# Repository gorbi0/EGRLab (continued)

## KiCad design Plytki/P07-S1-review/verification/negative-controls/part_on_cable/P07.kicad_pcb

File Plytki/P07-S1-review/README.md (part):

# P07 DRIVE — S1, schemat pod moduł IBT-2 (2 × BTS7960B)

*5.10.2026, sesja w chmurze według `Plytki/Format-S1/zadania/ZADANIE-P07-S1.md`. Baza: `origin/pelny-s1`. Pinout P04 R3 z `origin/p04-r3-pcb` (702732a7, `reference/P04-R3-J_BP.csv`).*

**Status (6.10): schemat z decyzjami użytkownika 5.10 i uproszczeniami 6.10 gotowy (ERC 0, kontrole 16/16 i 27/27). PCB NIEDOMKNIĘTE — po uproszczeniach 1–4 zostało 13 przerw sygnałowych (sekcja „PCB — stan”); paczki produkcyjnej nie ma.** Sprzętu nie zmontowano ani nie zmierzono. Moduł IBT-2 zmierzono tylko bez zasilania (POMIARY A–C); kroki D i E nie są zrobione.

## Co to jest

Płytka nośna testera w stosie S1: **poziom 5, sloty S2–S3, klasa 2/3 (106,5 × 100 mm)**. Moduł IBT-2 stoi poza stosem, na ściance obudowy, i łączy się z P07 taśmą 8 żył (J5) oraz czterema parami przewodów 2,0 mm² (J1–J4). Z v6.1 (Pololu 1451 / VNH5019) zostają: własny bocznik Kelvin 5 mΩ + INA240A2 + MCP3201 (ITEST), okno OC z zatrzaskiem, KPWR i otwarty kolektor na SAFE_N. To nie jest zamiana pin w pin. W trybie LOGGER mostek nie jest połączony z ECU — robi to dopiero port TEST na panelu (P11).

| Arkusz | Zawartość |
|---|---|
| P07 | 5VA_P07 (R50 10 Ω), 3V3A_P07 (MCP1702), odsprzęganie, arkusze |
| MOC | J1 VMOTOR, TVS SMCJ18A, C1 220 µF, KPWR K1 (G2RL-1-E **DC5, cewka z 5V_SYS**) z Q1 AO3400A, C9 10 µF i clampem 15 V do 5V_SYS, R4 1 k (wstępne ładowanie), J2 B+/B−, J3 M+/M−, RSH1, J4 TEST |
| ANA | R6/R7 Kelvin, INA240A2, MCP1525, U3 (bufor ADC + REF_BUF), dzielnik ITEST, U4 (OC_HIGH), TLV1702 |
| DIG | MCP3201 (posiadany DIP8), 74LVC125 SPI (DOUT trójstanowy), przejście SUP5 5 V → 3,3 V |
| LOGIKA | MCP120 ×2, odbiorniki Ioff 74LVC125 (od 6.10 tylko MOTOR_INA / INB), 74LVC14 (Schmitt), 3 × 74HC08, 74HC74 (OC_GOOD, NO_TRIP), Q2 na SAFE_N |
| MODUL | PTC → 5V_MOD, 74AHCT125 (3,3 → 5 V z OE), J5, R43 10 Ω w masie modułu, diagnostyka IS (dzielnik + clamp, próg na P03) |
| ZLACZA | J_BP1, J_BP2 |
| SERWIS | J_SV2 z 9 rezystorami przy węzłach (od 6.10; było J_SV1 + J_SV2, 20 kołków) |

Obliczenia: `docs/PROJEKT.md`. Wiązki: `docs/WIAZKA-MODUL.md`. BOM S1: `docs/BOM.csv`, `docs/zakupy.csv` (132 części + wiązka W5; z rejestru INA240A2, MCP3201-BI/P i 2 × 74LVC125AD, reszta nowa).

## Krawędź A (kontrakt dla P12)

| Pin | J_BP1 (S2, x płytki 26,5 / stosu 80,0) | J_BP2 (S3, x płytki 80,0 / stosu 133,5) |
|---|---|---|
| 2 | ADC_SCLK ← P03 | MOTOR_PERMIT ← P04 |
| 4 | ADC_DOUTA → P03 (wspólna, CS) | PWM_OUT ← P04 |
| 6 | CS_ITEST_N ← P03 | ARM_CLK ← P04 |
| 8 | MOTOR_INA ← P03 | DRIVE_OK → P04 |
| 10 | MOTOR_INB ← P03 | 5V_SYS |
| 12 | ENA_DIAG → P03 | 5V_SYS |
| 14 | ENB_DIAG → P03 | 3V3_IO |
| 16 | GND (rezerwa) | SAFE_N (węzeł OC) |

Nieparzyste piny to GND; złącza IDC 2 × 8 kątowe obudowane, pin 1 od mniejszego x. ADC_SCLK / ADC_DOUTA są na pinach 2/4 jak J_BP2 P03 R6, P05 R3 i J_BP P06 R2. Sieci P04 mają te same numery pinów co J_BP2 P04 R3 (2/4/6/8/16). **Dwa złącza zamiast jednego 2 × 10 z budżetu S1 §8:** 12 sygnałów i 3 piny zasilania nie mieszczą się w 10 parzystych pinach. Kierunki i drugi koniec: `docs/J_BP.csv`.

## Krawędź B (serwis)

Od 6.10 (uproszczenie 1) **jedna listwa J_SV2** (S3, x 63,5–96,5, 12 kołków): GND, 5V_SYS, 5VA_P07, 3V3A_P07, KPWR_COIL_LOW, SAFE_OK, OC_LOCAL_N, OC_GOOD, DRIVE_OK (1 k), GND, I_T_OUT (10 k), GND. Zwarcie kołka OC_LOCAL_N do GND (przez 1 k) wymusza OC — próba odbiorcza zatrzasku. RPWM / LPWM / EN / IS mierzy się na listwie modułu, która jest poza stosem. `docs/SERWIS.csv`.

## Kontrole (`src/run_schematic.py`; w chmurze `scripts/egrlab-docker python3 src/run_schematic.py`, ok. 1 min)

| Kontrola | Wynik |
|---|---|
| ERC | **0** na 8 arkuszach |
| Netlista pin po pinie względem `parts.py` | **448/448**, 132 części, 101 sieci (po uproszczeniach 6.10) |
| `verify_electrical.py` | **16/16**, mutacje **23/23**, próba zerowa czysta |
| `verify_s1.py` (S1 i kontrakty P12 / P03 R6 / P04 R3) | **27/27**, mutacje **26/26**, próba zerowa czysta (od 6.10 jedna listwa: 5 kontroli J_SV1 odpada, dochodzą `SV-ONLY-J_SV2` i `SRV-REQUIRED-NODES`) |
| Powierzchnia (`powierzchnia.py`) | 69 % metodą P06 R2 (tam 41 %); wnętrze bez złączy krawędzi 50 %, z 1206 od spodu 37 % |

`verify_electrical.py` symuluje logikę na wyeksportowanej netliście: modele bramek według wartości części, podciąganie przez najmniejszą rezystancję, komparator i nadzorcy jako otwarte kolektory, 74HC74 z PRE/CLR i zboczem. Tabela 2304 wierszy pokazuje, że **bez MOTOR_PERMIT, bez SAFE_N, przy OC albo złych szynach wszystkie wejścia modułu (RPWM, LPWM, R_EN, L_EN) są L**, a KPWR wyłączony. Do tego martwe szyny, otwarte taśmy, zawieszona bramka AND (blokuje ją OE bufora), 11 kroków sekwencji zatrzasku (brak samoczynnego uzbrojenia, ARM przy PERMIT = H nie uzbraja, ARM w trakcie OC nie kasuje), progi OC w narożnikach (+8,01…+8,11 A / −7,99…−8,03 A), skala ITEST, moce bocznika i R4, cewka 5 V z 5V_SYS, bramka Q1 i clamp KPWR, TVS, próg IS i rozdział mas. Raporty: `verification/QA.md`, `electrical-checks.json`, `s1-checks.json`, `powierzchnia.json`; PDF `output/pdf/P07-S1-schemat.pdf`.

## Decyzje (sporne oznaczone)

1. **Mapowanie VNH5019 → BTS7960:** RPWM = PWM & MOTOR_INA, LPWM = PWM & MOTOR_INB, R_EN = L_EN = DRIVE_EN. Hamowanie i stany INA = INB jak w VNH5019. Firmware bez zmian w sterowaniu.
2. **Blokada w trzech warstwach:** bramki AND (MOTOR_PERMIT · SAFE_N · OC_GOOD · RAILS_OK), OE bufora 74AHCT125 i KPWR. 74HC244 modułu jest stale aktywny (OE na GND), więc moduł sam niczego nie blokuje.
3. **DRIVE_OK = RAILS_OK & NO_TRIP** (nowy drugi przerzutnik). Przy starcie bez ARM DRIVE_OK = 1, więc INTERLOCK na P04 nie blokuje LOGGERA ani SENSOR. Po OC DRIVE_OK = 0 aż do ARM. v6.1 miało DRIVE_OK = RAILS_OK.
4. **Logika na 3V3_IO** (jak P04), analog na lokalnych 5VA / 3V3A (jak P06 R2). Odbiorniki z Ioff tylko tam, gdzie drugi koniec może mieć inne zasilanie (P03: MOTOR_INA/INB, CS, SCLK) oraz dla MOTOR_PERMIT / PWM_OUT. SAFE_N wchodzi przez 1 k na Schmitt 74LVC14 (zbocze RC ok. 10 µs na P04), bez podciągania na P07, z 1 M do GND (otwarta taśma = SAFE_OK L).
5. **R4 1 kΩ równolegle do styków KPWR (zostaje — decyzja użytkownika 5.10):** ładuje 330 µF modułu, żeby styk nie zamykał się na pusty kondensator (spawanie). Cena: przy otwartym KPWR B+ modułu jest na 91 % VMOTOR przez 1 k; prąd silnika ≤ 17 mA, przy zwarciu 0,28 W.
6. **KPWR to przekaźnik G2RL-1-E DC5 z cewką na 5V_SYS** (decyzja użytkownika 5.10; było DC12 z VMOTOR), nie tranzystor: galwaniczne odłączenie i brak strat przy 10 A (MOSFET z P02 dałby ok. 2 W bez radiatora). Cewka 80 mA przy 98–102 % napięcia znamionowego, Q1 AO3400A (źródło na GND, bramka wprost z 74HC08 przez 100 Ω — NPN potrzebowałby ok. 6 mA bazy z HC przy 3,3 V), clamp 1N4148W + 15 V do 5V_SYS (VDS ≤ 20,8 V), C9 10 µF przy cewce. Obwód cewki w domenie GND, styki w domenie PGND. Footprint bez zmian.
7. **Masy:** GND i PGND rozdzielone na P07, wspólny punkt na P02 R4. MOD_GND przez 10 Ω. Działa przy masie modułu połączonej z B− i przy rozdzielonej (`docs/PROJEKT.md`).
8. **Sporne — filtr ITEST τ 0,26 ms** (C7 100 nF C0G): antyaliasing przy 2 kS/s.
9. **OC ±8 A:** ≥ 115 % prądu pracy 6 A, poniżej nasycenia INA240A2 przy najniższym 5VA. „10 A w próbie” = bierna kwalifikacja toru jak w P06 (E15) — decyzja użytkownika 5.10; aktywny mostek nie podaje 10 A.
10. **ENA_DIAG / ENB_DIAG:** H = prąd gałęzi powyżej ok. 1,3–5,8 A (od 6.10: próg na wejściu P03, bez Schmitta) albo poziom błędu IS (przyjęte 5.10; firmware dostosuje się później). Znaczenie inne niż w VNH5019 (tam L = błąd).
11. Wyjątki od „nowe = SMD 1206”: R4 2512 (moc), C1 elektrolit, RSH1 2512 Kelvin (jak P06 R2), K1, MCP3201 w posiadanym DIP8, TO-92 jak w P06 R2.

## Wymagania dla layoutu (sesja lokalna)

- J4 (TEST) przy krawędzi x = 0; J1–J3 najlepiej tam samo, żeby pętla 10 A była krótka. Tor 10 A ≥ 4 mm na obu warstwach, zszyty przelotkami; bez przelotek w polach RSH1; para Kelvina jak w P06 R2.
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
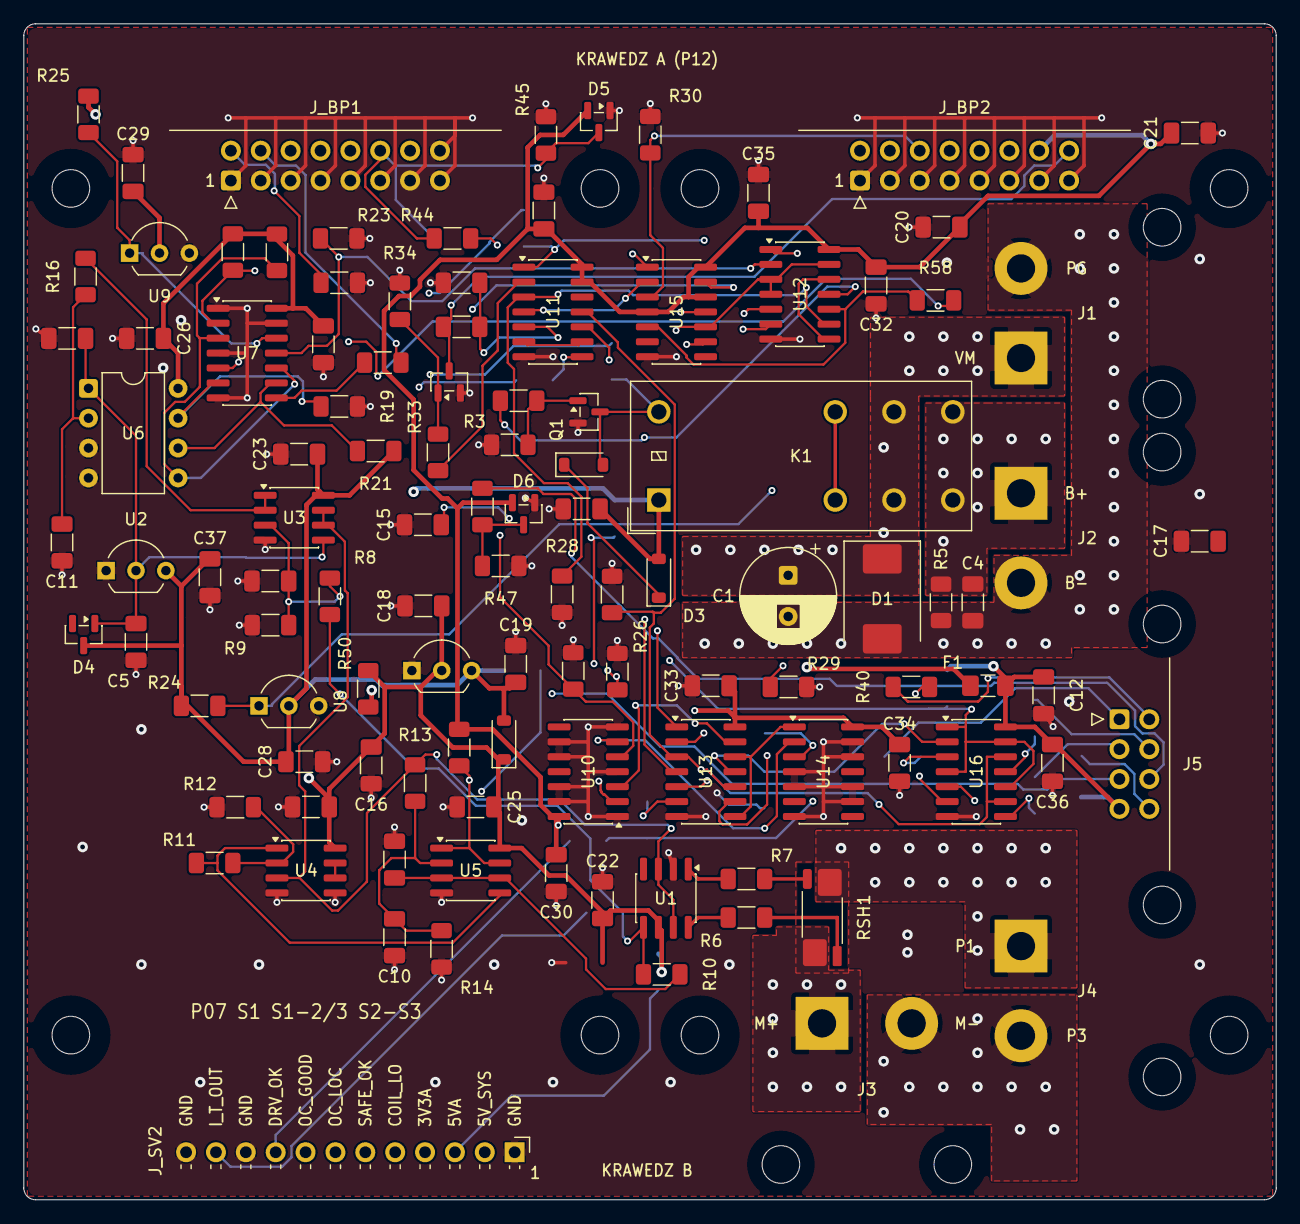
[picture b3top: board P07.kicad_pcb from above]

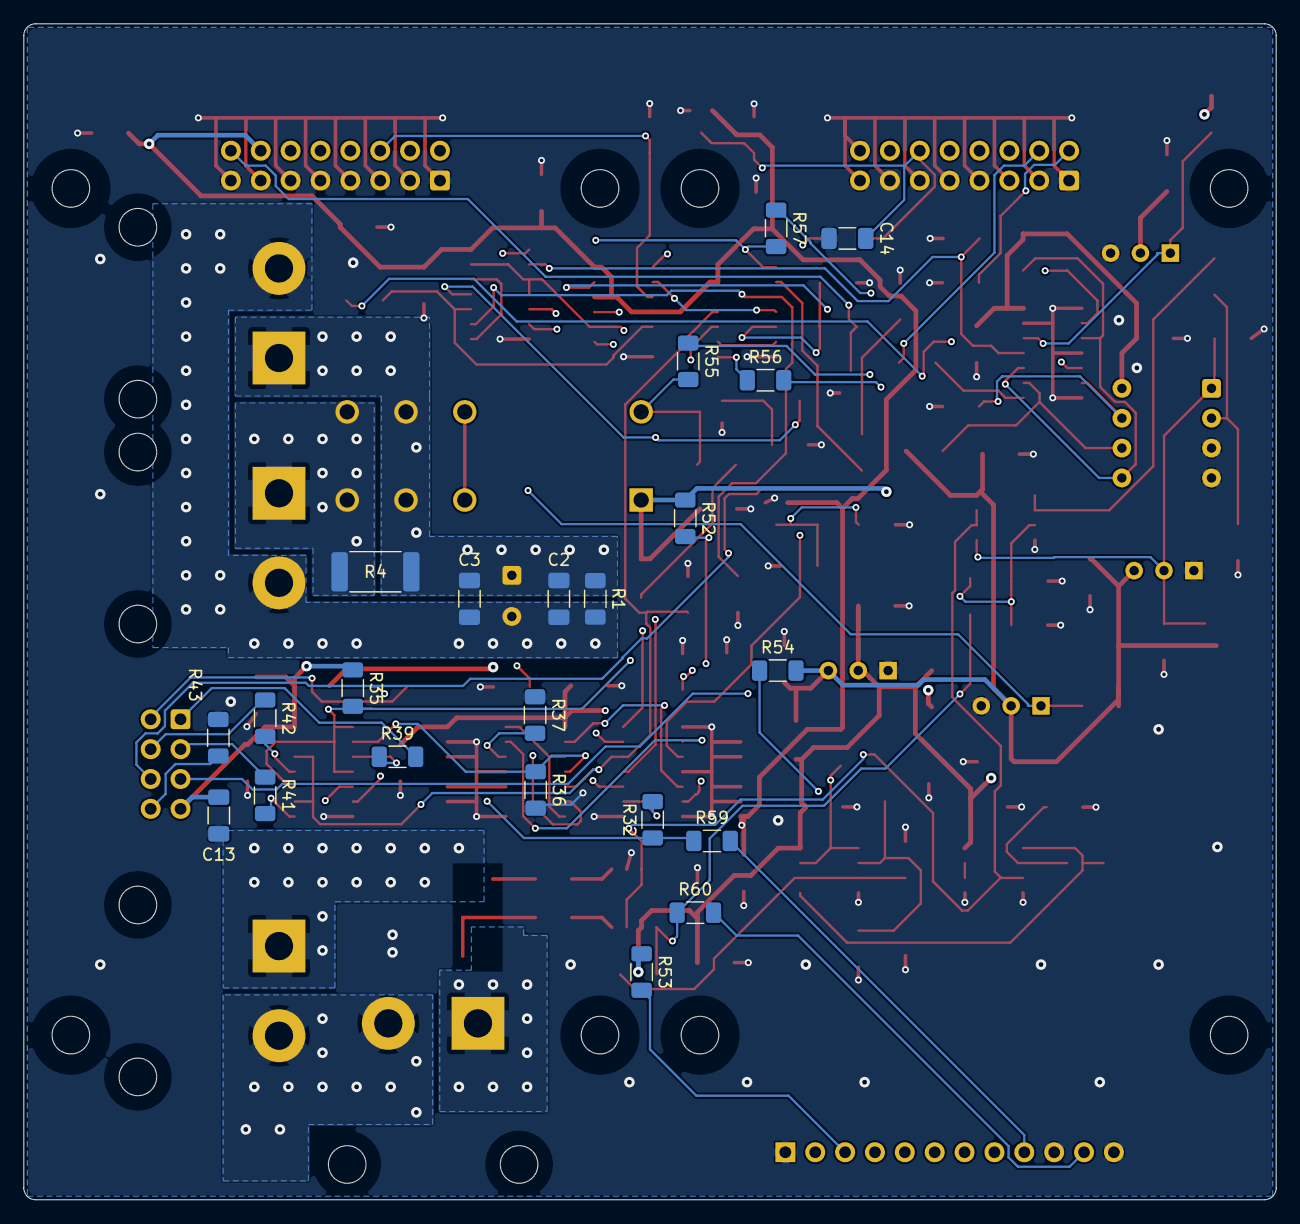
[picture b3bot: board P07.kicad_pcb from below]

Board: 4 copper layers, 106.5 x 100.0 mm, 140 parts (22 on the bottom side), 90 nets.

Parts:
C1: 220u; CP_Radial_D8.0mm_P3.50mm
C2, C18: 1u; C_1206_3216Metric_Pad1.33x1.80mm_HandSolder
C3, C4, C6, C7, C13, C14, C15, C17, C20, C22, C23, C24, C25, C26, C27, C28, C29, C30, C31, C32, C33, C34, C35, C36, C37: 100n; C_1206_3216Metric_Pad1.33x1.80mm_HandSolder
C5, C19: 4.7u; C_1206_3216Metric_Pad1.33x1.80mm_HandSolder
C8: 1n; C_1206_3216Metric_Pad1.33x1.80mm_HandSolder
C9, C12, C16, C21: 10u; C_1206_3216Metric_Pad1.33x1.80mm_HandSolder
C10: 10n; C_1206_3216Metric_Pad1.33x1.80mm_HandSolder
C11: 470p; C_1206_3216Metric_Pad1.33x1.80mm_HandSolder
D1: SMCJ18A; D_SMC
D2: 1N4148W; D_SOD-123
D3: BZT52C15; D_SOD-123
D4: BAT54; SOT-23
D5, D6: BAT54S; SOT-23
D7: B5819W; D_SOD-123
F1: PTC 0.12A; Fuse_1206_3216Metric_Pad1.42x1.75mm_HandSolder
H1, H2, H3, H4, H5, H6, H7, H8: M3 NPTH
J1: VMOTOR; PTH_VMOTOR
J2: MOD B+/B-; PTH_MODPWR
J3: MOD M+/M-; PTH_MODOUT
J4: TEST; PTH_TEST
J5: J_MOD; IDC-Header_2x04_P2.54mm_Horizontal
J_BP1: J_BP1; IDC-Header_2x08_P2.54mm_Horizontal
J_BP2: J_BP2; IDC-Header_2x08_P2.54mm_Horizontal
J_SV2: J_SV2 SERWIS 1x12; PinHeader_1x12_P2.54mm_Horizontal
K1: G2RL-1-E DC5; Relay_SPDT_Omron_G2RL-1-E
Q1: AO3400A; SOT-23
Q2: MMBT3904; SOT-23
R1, R5, R12, R14, R15, R18, R19, R23, R24, R25, R33, R60: 10K; R_1206_3216Metric_Pad1.30x1.75mm_HandSolder
R2, R32, R39, R40, R41, R42: 100R; R_1206_3216Metric_Pad1.30x1.75mm_HandSolder
R3, R17, R20, R26, R27, R28, R29, R30, R34, R35, R36, R37, R38, R45, R47: 100K; R_1206_3216Metric_Pad1.30x1.75mm_HandSolder
R4: 1K; R_2512_6332Metric_Pad1.40x3.35mm_HandSolder
R6, R7, R43, R50: 10R; R_1206_3216Metric_Pad1.30x1.75mm_HandSolder
R8, R9: 5.11K; R_1206_3216Metric_Pad1.30x1.75mm_HandSolder
R10, R31, R52, R53, R54, R55, R56, R57, R58, R59: 1K; R_1206_3216Metric_Pad1.30x1.75mm_HandSolder
R11: 8.06K; R_1206_3216Metric_Pad1.30x1.75mm_HandSolder
R13: 40.2K; R_1206_3216Metric_Pad1.30x1.75mm_HandSolder
R16, R22: 47R; R_1206_3216Metric_Pad1.30x1.75mm_HandSolder
R21: 47K; R_1206_3216Metric_Pad1.30x1.75mm_HandSolder
R44, R46: 4K7; R_1206_3216Metric_Pad1.30x1.75mm_HandSolder
R51: 1M; R_1206_3216Metric_Pad1.30x1.75mm_HandSolder
RSH1: 5m; R_Shunt_Vishay_WSK2512_T1.19mm_SenseE1.70
U1: INA240A2; SOIC-8_3.9x4.9mm_P1.27mm
U2: MCP1525-I/TO; TO-92_Inline_Wide
U3, U4: MCP6022-I/SN; SOIC-8_3.9x4.9mm_P1.27mm
U5: TLV1702AIDR; SOIC-8_3.9x4.9mm_P1.27mm
U6: MCP3201-BI/P; DIP-8_W7.62mm
U7, U10: 74LVC125AD; SOIC-14_3.9x8.7mm_P1.27mm
U8: MCP120-300DI/TO; TO-92_Inline_Wide
U9: MCP120-450DI/TO; TO-92_Inline_Wide
U11: 74LVC14AD; SOIC-14_3.9x8.7mm_P1.27mm
U12, U13, U14: SN74HC08D; SOIC-14_3.9x8.7mm_P1.27mm
U15: SN74HC74D; SOIC-14_3.9x8.7mm_P1.27mm
U16: 74AHCT125D; SOIC-14_3.9x8.7mm_P1.27mm
U18: MCP1702-3302E/TO; TO-92_Inline_Wide

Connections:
3V3A_P07: C19.1, C23.1, C26.1, C27.1, C28.1, C37.1, D4.3, D7.2, R17.1, R18.1, R21.1, R24.1, R54.1, U2.3, U3.8, U6.8, U7.14, U8.2, U18.3
3V3_IO: C20.1, C21.1, C30.1, C31.1, C32.1, C33.1, C34.1, C35.1, D5.2, D6.2, J_BP2.14, R15.2, U10.14, U11.13, U11.14, U12.14, U13.14, U14.14, U15.4, U15.12, U15.14
5VA_P07: C16.1, C17.1, C18.1, C22.1, C24.1, C25.1, C29.1, D7.1, R25.1, R50.2, R53.1, U1.6, U4.8, U5.8, U9.2, U18.2
5V_MOD: C12.1, C13.1, C36.1, F1.2, J5.7, R35.1, U16.14
5V_SYS: C9.1, D3.2, F1.1, J_BP2.10, J_BP2.12, K1.A1, R50.1, R52.1
/ANA/INA_MINUS: R7.2, U1.1
/ANA/INA_PLUS: R6.2, U1.8
/ANA/I_DIV: C7.1, R8.2, R9.1, U3.3
/ANA/I_FILT: C8.1, R10.2, U5.3, U5.6
/ANA/OC_FB: R11.2, R12.1, U4.2
/ANA/OC_HIGH: R11.1, U4.1, U5.5
/ANA/OC_LOW: C10.1, R13.2, R14.1, U5.2
/ANA/OC_UNUSED: U4.6, U4.7
/ANA/REF_BUF: R13.1, U1.3, U1.7, U3.6, U3.7, U4.3
/DIG/ADC_AIN: C11.1, R16.2, U6.2
/DIG/ADC_DOUT: R21.2, U6.6, U7.9
/DIG/CLK_LOCAL: R19.1, U6.7, U7.6
/DIG/CS_LOCAL_N: R18.2, U6.5, U7.3, U7.10
/DIG/DOUT_TX: R22.1, U7.8
/LOGIKA/DRIVE_OK_L: R32.1, U13.6
/LOGIKA/INA_P07: U10.3, U13.13
/LOGIKA/INB_P07: U10.6, U14.2
/LOGIKA/LOCAL_CLEAR_N: U12.6, U15.1
/LOGIKA/NO_TRIP: U13.5, U15.9
/LOGIKA/OC_B: Q2.1, R33.2, R34.1
/LOGIKA/OC_FAULT: R33.1, U11.2
/LOGIKA/PERMIT_ARMED: U12.8, U12.12
/LOGIKA/PERMIT_N: U11.4, U15.2
/LOGIKA/PWM_EN: U13.8, U13.12, U14.1
/LOGIKA/RAILS_OK: U12.3, U12.4, U12.13, U13.4, U15.10
/LOGIKA/SAFE_BAD: U11.6, U11.9
/LOGIKA/SAFE_SENSE: R31.2, R51.1, U11.5
/LOGIKA/SUP3_N: R24.2, U8.1, U12.1
/MOC/KPWR_B: Q1.1, R2.2, R3.1
/MOC/KPWR_CLAMP: D2.1, D3.1
/MOC/MOD_BP: C4.1, J2.1, K1.14, R4.2, R5.1
/MOC/MOD_MP: J3.1, RSH1.1
/MOC/T_EGR_P1: J4.1, RSH1.4
/MOC/T_EGR_P3: J3.2, J4.2
/MODUL/LEN_D: R42.1, U16.11
/MODUL/LPWM: J5.2, R40.2
/MODUL/LPWM_D: R40.1, U16.6
/MODUL/L_EN: J5.4, R42.2
/MODUL/L_IS: J5.6, R46.1
/MODUL/MOD_GND: J5.8, R43.2
/MODUL/REN_D: R41.1, U16.8
/MODUL/RPWM: J5.1, R39.2
/MODUL/RPWM_D: R39.1, U16.3
/MODUL/R_EN: J5.3, R41.2
/MODUL/R_IS: J5.5, R44.1
/SERWIS/SRV_3V3A_P07: J_SV2.4, R54.2
/SERWIS/SRV_5VA_P07: J_SV2.3, R53.2
/SERWIS/SRV_5V_SYS: J_SV2.2, R52.2
/SERWIS/SRV_DRIVE_OK: J_SV2.9, R59.2
/SERWIS/SRV_I_T_OUT: J_SV2.11, R60.2
/SERWIS/SRV_KPWR_COIL_LOW: J_SV2.5, R55.2
/SERWIS/SRV_OC_GOOD: J_SV2.8, R58.2
/SERWIS/SRV_OC_LOCAL_N: J_SV2.7, R57.2
/SERWIS/SRV_SAFE_OK: J_SV2.6, R56.2
ADC_BUF: R16.1, U3.1, U3.2
ADC_DOUTA: J_BP1.4, R22.2
ADC_SCLK: J_BP1.2, R20.1, U7.5
ARM_CLK: J_BP2.6, R30.1, U15.3, U15.11
CS_ITEST_N: J_BP1.6, R17.2, U7.2
DRIVE_EN: R38.1, U11.11, U13.3, U13.10, U16.9, U16.12
DRIVE_OK: J_BP2.8, R32.2, R59.1
DRV_OFF: R35.2, U11.10, U16.1, U16.4, U16.10, U16.13
ENA_DIAG: C14.1, D5.3, J_BP1.12, R44.2, R45.1
ENB_DIAG: C15.1, D6.3, J_BP1.14, R46.2, R47.1
GND: C5.2, C6.2, C7.2, C8.2, C9.2, C10.2, C11.2, C12.2, C13.2, C14.2, C15.2, C16.2, C17.2, C18.2, C19.2, C20.2, C21.2, C22.2, C23.2, C24.2, C25.2, C26.2, C27.2, C28.2, C29.2, C30.2, C31.2, C32.2, C33.2, C34.2, C35.2, C36.2, C37.2, D5.1, D6.1, J_BP1.1, J_BP1.3, J_BP1.5, J_BP1.7, J_BP1.9, J_BP1.11, J_BP1.13, J_BP1.15, J_BP1.16, J_BP2.1, J_BP2.3, J_BP2.5, J_BP2.7, J_BP2.9, J_BP2.11, J_BP2.13, J_BP2.15, J_SV2.1, J_SV2.10, J_SV2.12, Q1.2, Q2.2, R3.2, R9.2, R12.2, R14.2, R19.2, R20.2, R23.2, R26.2, R27.2, R28.2, R29.2, R30.2, R34.2, R36.2, R37.2, R38.2, R43.1, R45.2, R47.2, R51.2, U1.2, U2.1, U3.4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
I_T_OUT: R8.1, R10.1, R60.1, U1.5
KPWR_COIL_LOW: D2.2, K1.A2, Q1.3, R55.1
K_MINUS: R7.1, RSH1.3
K_PLUS: R6.1, RSH1.2
LOCAL_PERMIT: R2.1, U12.11, U13.1
LPWM_L: R37.1, U14.3, U16.5
MOTOR_INA: J_BP1.8, R26.1, U10.2
MOTOR_INB: J_BP1.10, R27.1, U10.5
MOTOR_PERMIT: J_BP2.2, R28.1, U11.3, U12.9
OC_GOOD: R58.1, U12.10, U15.5
OC_LOCAL_N: R15.1, R57.1, U5.1, U5.7, U11.1, U12.5, U15.13
PGND: C1.2, C2.2, C3.2, C4.2, D1.2, J1.2, J2.2, R1.2, R5.2
PWM_OUT: J_BP2.4, R29.1, U13.9
REF25: C5.1, C6.1, D4.1, U2.2, U3.5, U6.1
RPWM_L: R36.1, U13.11, U16.2
SAFE_N: J_BP2.16, Q2.3, R31.1
SAFE_OK: R56.1, U11.8, U13.2
SUP5_N: R23.1, U7.11, U12.2
SUP5_RAW: R25.2, U7.12, U9.1
VMOTOR: C1.1, C2.1, C3.1, D1.1, J1.1, K1.11, R1.1, R4.1

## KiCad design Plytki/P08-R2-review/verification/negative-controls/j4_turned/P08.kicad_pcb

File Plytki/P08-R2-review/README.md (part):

# P08 R2 — SENSOR w formacie S1 (schemat i PCB)

5.10.2026, sesja w chmurze, zadanie `Plytki/Format-S1/zadania/ZADANIE-P08-S1.md`. Schemat z sesji w chmurze; **PCB 5.10.2026 lokalnie** (Ubuntu 24/7, KiCad 10.0.6 w Dockerze; sekcja „PCB”), paczka zamówieniowa `Plytki/P08-PCB-R2-zamowienie`. Sprzęt NIE ZBADANY. R2 powstała na kopii generatora z `Plytki/P08-R1-review` (zamknięty pakiet, niezmieniony).

**Klasa płytki:** 1/3 (53 × 100 mm), **slot S1 poziomu 5** (S1-3, wariant pełny; S2–S3 tego poziomu zajmie P07). Poziom 5 nie jest wysoki: od góry ≤ 16,5 mm, od spodu tylko SMD ≤ 1,5 mm bez SOIC.

**Obwód R1 bez zmian:** TPS2553 (limit ok. 99–139 mA), przekaźnik G6K-2P-Y rozłączający plus i powrót, TBD62083, nadzorcy MCP120 (U6, U7 i strażnik EN U8), bramki HC08, bufory 74LVC125 z Ioff. Kontrola `R1-CIRCUIT-PARITY` porównuje każdy pin każdej części obwodu z netlistą R1 (`reference/P08-R1.xml`): 0 różnic, wartości te same. Opis działania i obliczenia: `docs/PROJEKT.md` (z R1).

## Zmiany R1 → R2

| Element | R1 | R2 |
|---|---|---|
| Połączenia z P02 / P04 / P03 | wiązki lutowane: J1 LV08 (Mini-Fit 4p), J2 SENSOR (IDC6, KEY2), J3 SFAULT (IDC6, KEY3) | **J1 = J_BP**, kątowe obudowane IDC **2×8** na krawędzi A, środek x = 26,5 mm, pin 1 od mniejszego x; nieparzyste GND |
| J4 TSENSOR | Mini-Fit Jr 2p na płytce, wiązka W4 po stronie P11 | **pole przewodów** 2 × AWG22 z kotwą 12 mm przy krawędzi x = 0 (strona panelu), para do portu TEST na panelu; numeracja J4 i pinów bez zmian |
| Punkty pomiarowe | TP1–TP13 (pola) | **J2 = listwa serwisowa** kątowa 1×13 na krawędzi B, GND na 1 i 13, 11 kołków przez R19–R29 przy węzłach (1 kΩ; TPS_EN 10 kΩ) |
| Rezystory | DIN0207 leżące | nowe **SMD 1206**; posiadane **R15 4,7 k (MF0207)** i **R16 6,8 k (MF0204)** na stojąco |
| Kondensatory | 0805, C10 elektrolit | nowe **SMD 1206 X7R**; C10 22 µF/25 V elektrolit bez zmian (nowy, bo dwa z rejestru bierze P02 R4) |
| U4/U5 SOIC14 | przez adapter SO14 | lutowane wprost od góry |
| Obrys | 100 × 80 mm | 53 × 100 mm, otwory slotu M3 wg S1 (rysuje layout) |

### J_BP (`docs/J_BP.csv`)

| Pin | Sieć | Pin | Sieć |
|---|---|---|---|
| 1 | GND | 2 | 5V_SYS |
| 3 | GND | 4 | 3V3_IO |
| 5 | GND | 6 | SENSOR_PERMIT (wejście, z P04) |
| 7 | GND | 8 | SENSOR_OK (wyjście, do P04) |
| 9 | GND | 10 | SENSOR_HEALTHY (wyjście, do P03 R6 J_BP1.12) |
| 11 | GND | 12 | GND (zapas masy) |
| 13 | GND | 14 | GND (zapas masy) |
| 15 | GND | 16 | 5V_SYS |

Nazwy sieci dokładnie jak w `P08-R1-review/docs/interfejsy.csv` i `P04-R2.2-review` J4 (SENSOR_PERMIT, SENSOR_OK) oraz w P03 R6 J_BP1.12 (SENSOR_HEALTHY, wejście P03; w kontraktach P12 „czeka na P08”). P12 łączy po nazwie.

### Listwa serwisowa (`docs/SERWIS.csv`)

1 GND, 2 5V_SYS, 3 3V3_IO, 4 SUP3_N, 5 SUP5_N, 6 SENSOR_OK, 7 SENSOR_HEALTHY, 8 PERMIT_LOCAL, 9 SENSOR_LOCAL, 10 TPS_EN (10 kΩ), 11 SENSOR_LIMITED, 12 SENSOR_FAULT_LOCAL_N, 13 GND. Pin 1 od większego x (kątowa listwa od góry; jak P09/P10 R2). Formularz odbioru z mapą TP R1 → kołki: `docs/ODBIOR.md`.

## Wyniki (`verification/QA.md`)

| Kontrola | Wynik |
|---|---|
| ERC (4 arkusze A3) | 0 naruszeń |
| Netlista pin po pinie względem `parts.py` | 52 części, 194 piny, 49 sieci, 0 błędów |
| Kontrole elektryczne | 49/49 PASS — obwód R1 (TPS, K1, U8, bramki, tabela prawdy 16 przypadków na rzeczywistych pinach, marginesy dzielnika EN) oraz nowe: J_BP (2×8, nieparzyste GND, zapasowe 12/14 GND bez sieci NC, format CSV jak P06 R2, ciągłość z trzema wiązkami R1, 5V_SYS ×2, kierunki, zgodność z CSV), kontrakty nazw z P04 R2.2 / P03 R6 / P02 R4 / P12, J4, listwa (≤ 13, GND na końcach, rezystor przy węźle, wartości, pokrycie ODBIOR, brak kołka na wyjściu czujnika), źródła części, zgodność obwodu z R1 |
| Próby ujemne | 49/49 mutacji wykrytych, próba zerowa czysta |
| Ocena powierzchni (`src/powierzchnia.py`, bez rozmieszczenia) | suma prostokątów obrysów 2356 mm² wobec 4486 mm² użytecznych (53 %); bez J1 i J2, które leżą w odjętych już pasach krawędzi A/B, ok. 1490 mm² (33 %) |

## Decyzje (sporne oznaczone)

1. **Sporne: J_BP 2×8, nie 2×5 z budżetu S1 §8.** Trzy sygnały + 5V_SYS ×2 (S1 §5) + 3V3_IO to 6 pinów parzystych, a 2×5 ma 5. Przyjęte przez użytkownika 5.10 (2×8 zostaje); wolne piny 12 i 14 są dodatkową masą w taśmie, a nie siecią „NC” (kontrakty P12 widziałyby ją jako sieć z jednym końcem).
2. **5V_SENSOR i AGND_SENSOR nie są na listwie** (przyjęte 5.10) (w R1 były TP12/TP13). Listwa mieści 11 węzłów, a kołek AGND_SENSOR obok GND pozwoliłby zsuniętą sondą ominąć styk powrotu K1. Wyjście mierzy się różnicowo na porcie TEST (para J4), tak jak R1 i tak wymagał (WIAZKI R1). Zwolnione miejsce bierze PERMIT_LOCAL (próba E10).
3. TPS_EN przez 10 kΩ (węzeł dzielnika R15/R16, S1 §6); pozostałe kołki przez 1 kΩ, także węzły z podciąganiem 10 kΩ (SUP3_N, SUP5_N, FAULT_N) — zwarcie kołka do GND tylko wymusza stan „niegotowe”, nic nie uszkadza.
4. J4 zachowuje numer i piny R1 (kontrakt W4 do P11); pole przewodów zamiast Mini-Fit, kotwa przy krawędzi x = 0 jak J4/J6 w P05 R3.
5. Posiadane THT według bilansu rejestru (`docs/ZAKUPY.md`): R15 MF0207 4,7 k i R16 MF0204 6,8 k (ostatnia sztuka), U3/U4/U5/U6/U7/D1 z przydziału P08. **U8 (drugi MCP120-300) trzeba dokupić** — zamówienie z 24.09 miało jedną sztukę dla P08.
6. U2 zostaje TBD62083APG w DIP18 (obwód R1 bez zmian), choć jest największą częścią poza złączami (ok. 230 mm² obrysu).

## PCB (5.10.2026; `src/run_release.py`, KiCad 10.0.6 w Dockerze)

| Kontrola | Wynik | Raport |
|---|---|---|
| DRC świeży, wszystkie poziomy, ze zgodnością ze schematem | 0 niepołączonych, 0 niezgodności, 0 innych naruszeń; 2 × `lib_footprint_mismatch` (J1, J2: nadruk przycięty przez `silkscreen.py`, przyjęte jawnie) | `verification/drc.json` |
| Kontrole PCB (`verify_pcb.py`) | 28/28 | `verification/pcb-checks.json`, `QA-PCB.md` |
| Próby ujemne PCB | 27/27 z próbą zerową | `verification/negative-controls.json` |
| Trasowanie | Freerouting 2.1.0 (GND jako płaszczyzna B.Cu), pierwsza próba; zablokowane: tor czujnika, wiązanie C1–U1.2 z przelotką, odsprzęganie U6–U8; planer: 1 trasa, 2 wiązania powrotu GND (`--ties`); 65 przelotek; ścieżki F.Cu 1,11 m, B.Cu 0,53 m | `routing/attempts.json`, `completion-routes.json`, `return-ties.json` |

**Zajętość:** obrysy części od góry 2168 mm² z 5146 mm² użytecznych (42 %; bez J1 / J2 w pasach krawędzi 1311 mm², 25 %), od spodu 121 mm² (tylko R19–R29). Obwód zmieścił się w klasie 1/3 z zapasem: dolna ćwiartka płytki (y 75–93) jest pusta.

Łańcuch: skrypty generyczne z P05 R3 (po recenzji 2.10: `complete_routes.py --ties`, `stitch.py --targeted`, `trim_stubs.py`, `gndpath.py`), części 1/3 z P10 R2 / P09 R2 (`silkscreen.py`, `verify_pcb.py`, `negative_controls.py`, `make_pdf.py`), wartości płytki w `src/board.py`. `run_release.py` odtwarza zapisany wynik routera (`routing/P08.ses`) i trasy planera. PDF (5 stron) obejrzany 5.10.2026.

**Decyzje (sporne oznaczone):**
1. Rozmieszczenie: blok czujnika przy panelu (x = 0) — J4, K1, U1, D1, U2, U8 / R15 / R16; logika pod J1 (U5 wejście / HEALTHY, U4 nadzorca 5 V / OK, U3 HC08, U6 / U7 w prawej kolumnie). Od spodu tylko rezystory serwisowe R19–R29 (SMD 1206, ≥ 1 mm od pól THT); U4 / U5 SOIC i U1 SOT-23-6 od góry (poziom 5: od spodu bez SOIC).
2. **J4 (para W4 do portu TEST)** obrócone tak, że kotwa opaski (2 × Ø3,2) leży 12 mm od pól w stronę panelu, krawędź otworu 1,9 mm od x = 0 (kontrola 1,5–6 mm, jak J4 / J6 P05 R3); Ø6 bez miedzi wokół otworów kotwy na obu warstwach. Pole 1 (5V_SENSOR, kwadratowe, nadruk „1”) pod polem 2 (AGND_SENSOR).
3. **Tor czujnika przez K1 zablokowany, 0,6 mm:** U1.6 → K1.3 3,6 mm, K1.4 → J4.1 (5V_SENSOR, F.Cu) 7,2 mm, K1.5 → J4.2 (AGND_SENSOR, B.Cu) 5,3 mm — linie plusa i powrotu krzyżują się na różnych warstwach (wszystkie końce to pola PTH). Styk powrotu K1.6 połączony z wylewką GND bez mostków termicznych. Klasa PWR (0,6 / 0,3 mm) obejmuje 5V_SYS i trzy sieci toru; kontrola szerokości: 5V_SYS ≥ 0,6, tor ≥ 0,5 mm.
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
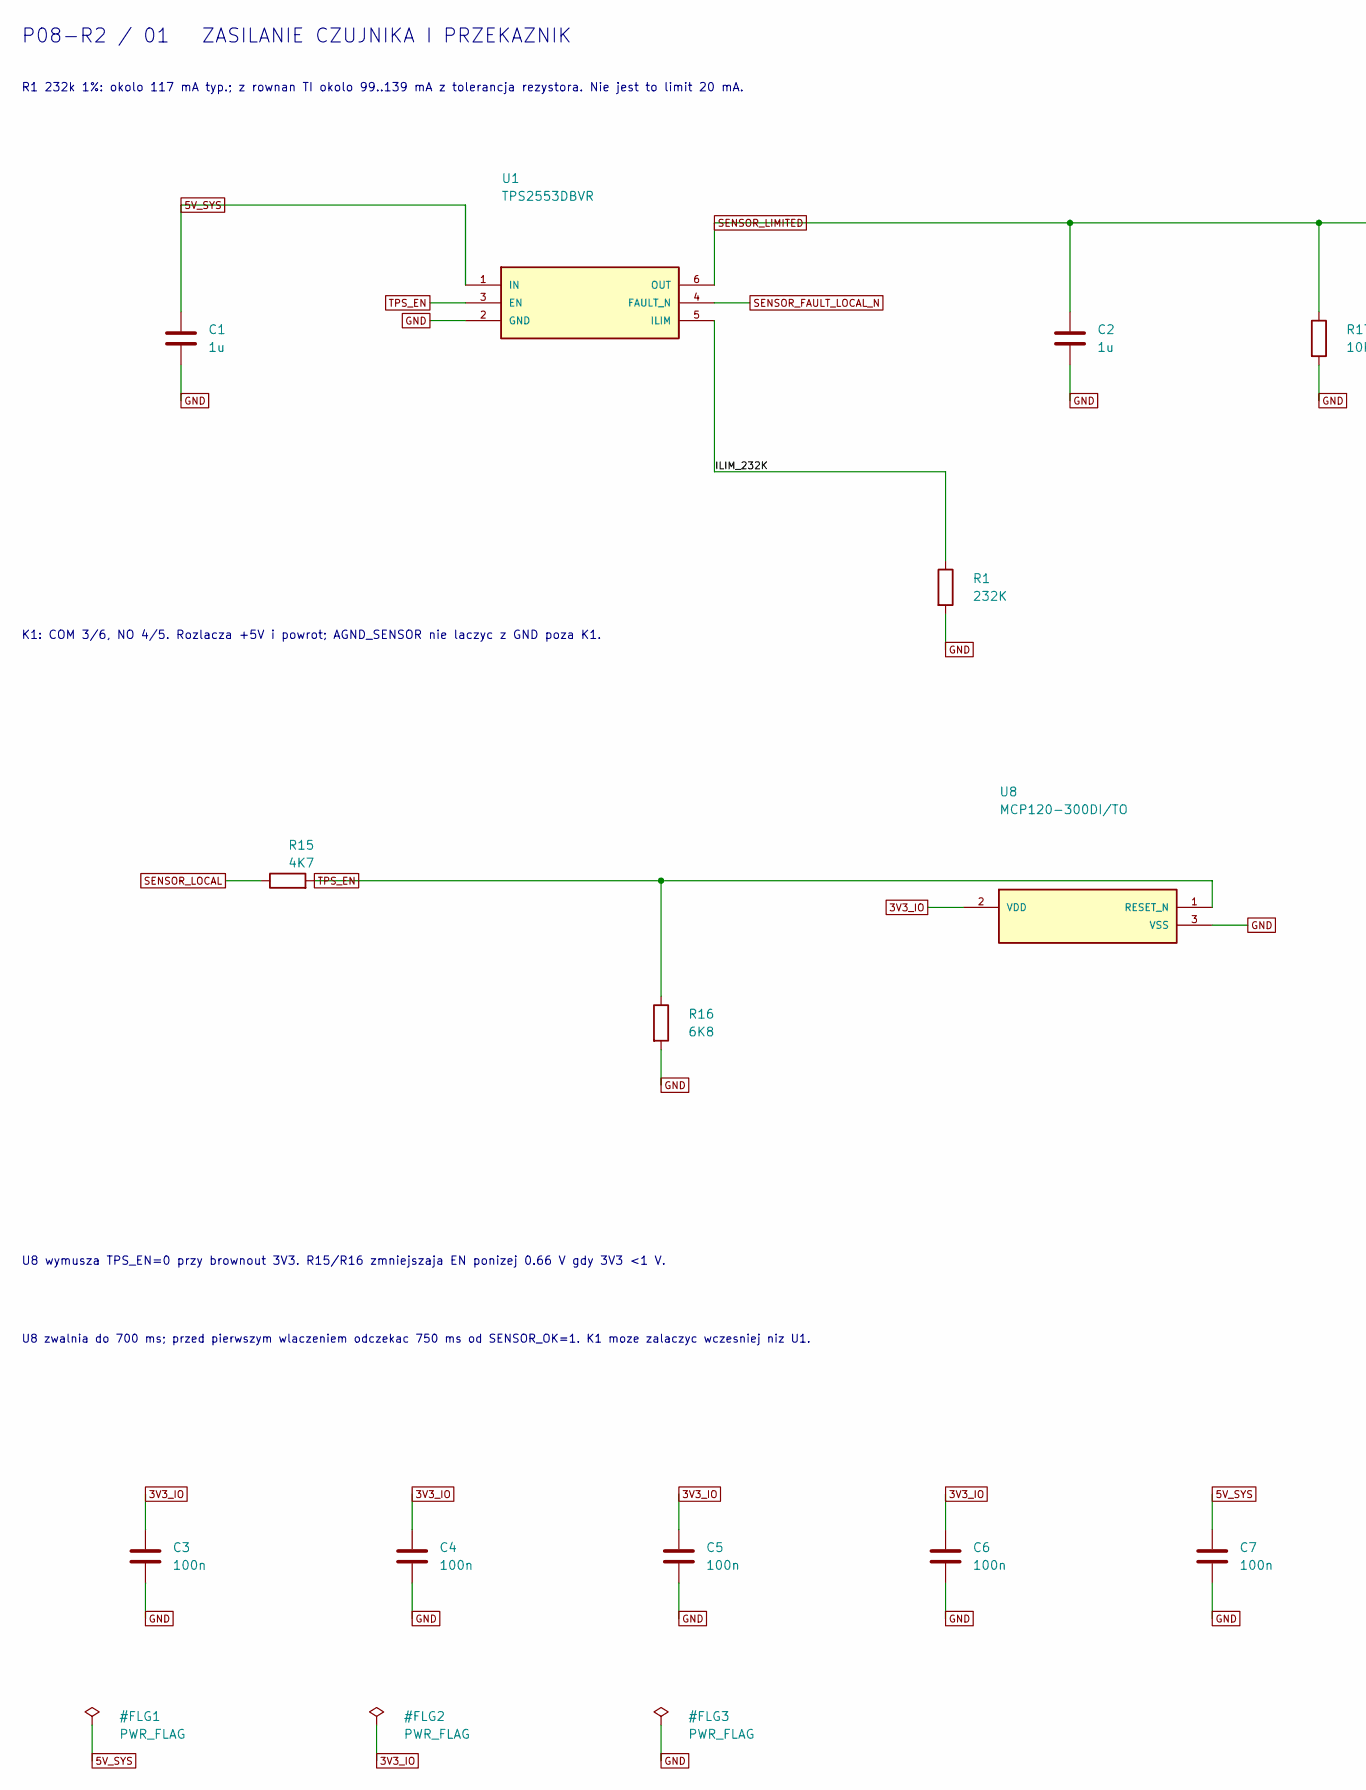
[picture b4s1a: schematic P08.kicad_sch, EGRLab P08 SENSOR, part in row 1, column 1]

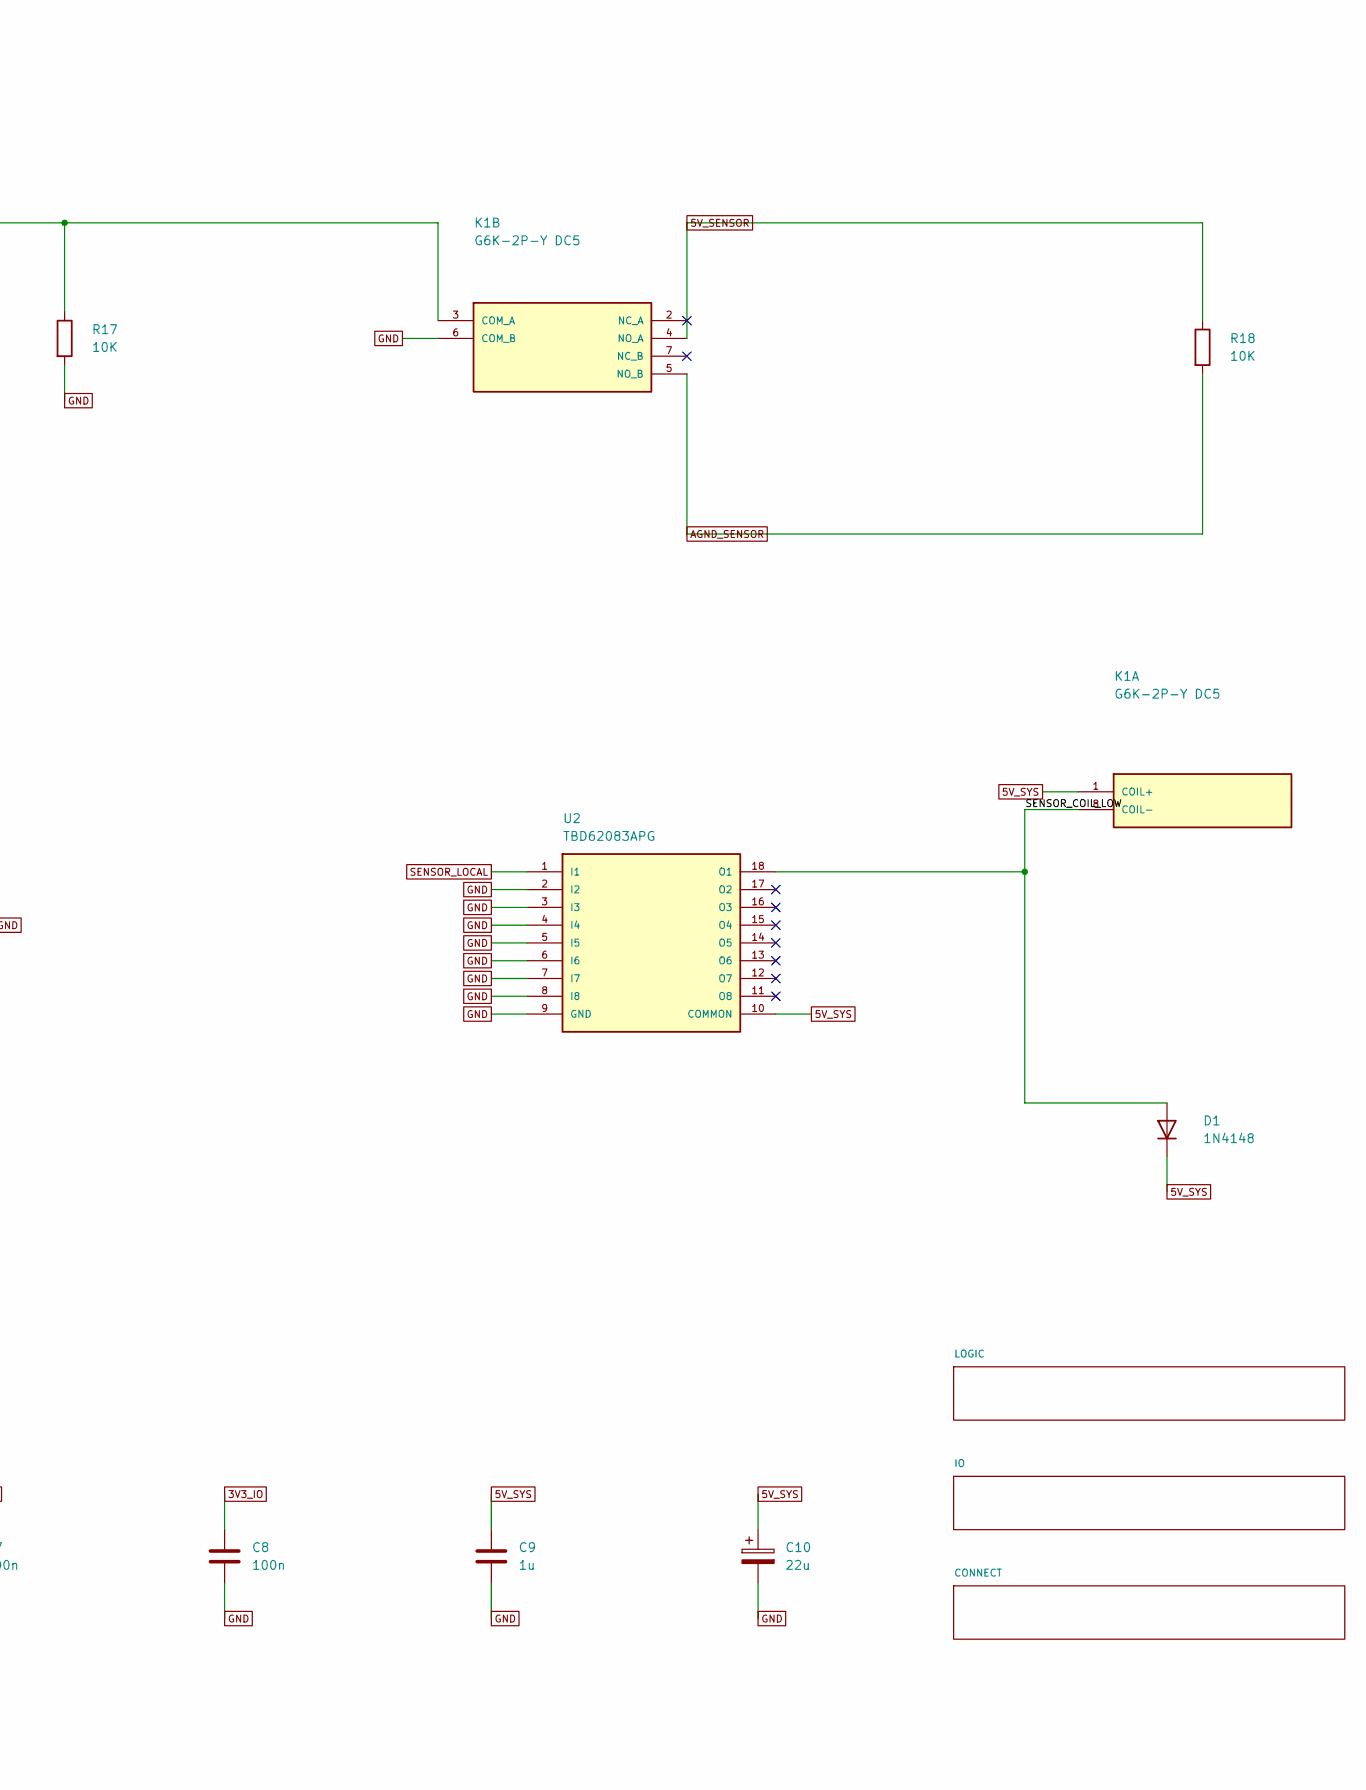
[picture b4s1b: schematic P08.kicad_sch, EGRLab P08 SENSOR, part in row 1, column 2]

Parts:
C1, C2, C9: 1u; C_1206_3216Metric_Pad1.33x1.80mm_HandSolder; MPN SMD 1206 X7R 25V 10% 1u
C3, C4, C5, C6, C7, C8: 100n; C_1206_3216Metric_Pad1.33x1.80mm_HandSolder; MPN SMD 1206 X7R 25V 10% 100n
C10: 22u; CP_Radial_D5.0mm_P2.00mm; MPN EEUFR1E220
D1: 1N4148; D_DO-35_SOD27_P7.62mm_Horizontal; MPN 1N4148
K1: G6K-2P-Y DC5; G6K_2P_Y_verified; MPN G6K-2P-Y DC5
R1: 232K; R_1206_3216Metric_Pad1.30x1.75mm_HandSolder; MPN SMD 1206 1% 0.25W 232K
R15: 4K7; R_Axial_DIN0207_L6.3mm_D2.5mm_P5.08mm_Vertical; MPN MF0207FTE-4K7 Yageo 4.7k 1% 0.6W (owned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
R16: 6K8; R_Axial_DIN0204_L3.6mm_D1.6mm_P2.54mm_Vertical; MPN MF0204FTE52-6K8 Yageo 6.8k 1% 0.4W (own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
R17, R18: 10K; R_1206_3216Metric_Pad1.30x1.75mm_HandSolder; MPN SMD 1206 1% 0.25W 10K
U1: TPS2553DBVR; SOT-23-6; MPN TPS2553DBVR
U2: TBD62083APG; DIP-18_W7.62mm; MPN TBD62083APG
U8: MCP120-300DI/TO; TO-92_Inline_Wide; MPN MCP120-300DI/TO

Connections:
3V3_IO: C3.1, C4.1, C5.1, C6.1, C8.1, U8.2 (VDD); also elsewhere on the board
5V_SENSOR: K1.4 (NO_A), R18.1; also elsewhere on the board
5V_SYS: C1.1, C7.1, C9.1, C10.1, D1.1 (K), K1.1 (COIL+), U1.1 (IN), U2.10 (COMMON); also elsewhere on the board
/ILIM_232K: R1.1, U1.5 (ILIM)
/SENSOR_COIL_LOW: D1.2 (A), K1.8 (COIL-), U2.18 (O1)
AGND_SENSOR: K1.5 (NO_B), R18.2; also elsewhere on the board
GND: C1.2, C2.2, C3.2, C4.2, C5.2, C6.2, C7.2, C8.2, C9.2, C10.2, K1.6 (COM_B), R1.2, R16.2, R17.2, U1.2 (GND), U2.2 (I2), U2.3 (I3), U2.4 (I4), U2.5 (I5), U2.6 (I6), U2.7 (I7), U2.8 (I8), U2.9 (GND), U8.3 (VSS); also elsewhere on the board
SENSOR_FAULT_LOCAL_N: U1.4 (FAULT_N); also elsewhere on the board
SENSOR_LIMITED: C2.1, K1.3 (COM_A), R17.1, U1.6 (OUT); also elsewhere on the board
SENSOR_LOCAL: R15.1, U2.1 (I1); also elsewhere on the board
TPS_EN: R15.2, R16.1, U1.3 (EN), U8.1 (RESET_N); also elsewhere on the board

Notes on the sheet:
R1 232k 1%: okolo 117 mA typ.; z rownan TI okolo 99..139 mA z tolerancja rezystora. Nie jest to limit 20 mA.
K1: COM 3/6, NO 4/5. Rozlacza +5V i powrot; AGND_SENSOR nie laczyc z GND poza K1.
U8 wymusza TPS_EN=0 przy brownout 3V3. R15/R16 zmniejszaja EN ponizej 0.66 V gdy 3V3 <1 V.
U8 zwalnia do 700 ms; przed pierwszym wlaczeniem odczekac 750 ms od SENSOR_OK=1. K1 moze zalaczyc wczesniej niz U1.
P08-R2 / 01 ZASILANIE CZUJNIKA I PRZEKAZNIK
